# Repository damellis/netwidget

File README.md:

Examples of connected (internet of things) devices, built using the Arduino software, Eagle circuit design software, the ATmega1284P microcontroller, and the CC3000 wifi module.

The master branch contains just the files common to all the examples. See the following branches for the individual examples:

* display: has a screen to show the weather or other online data (https://github.com/damellis/netwidget/tree/display)
* pair: each device has touch sensing and an RGB LED to allow remote communication (https://github.com/damellis/netwidget/tree/pair)
* sensor: logging temperature sensor data to data.sparkfun.com (https://github.com/damellis/netwidget/tree/sensor)

For more information, see: http://diy-devices.com/workshops/connected-devices/

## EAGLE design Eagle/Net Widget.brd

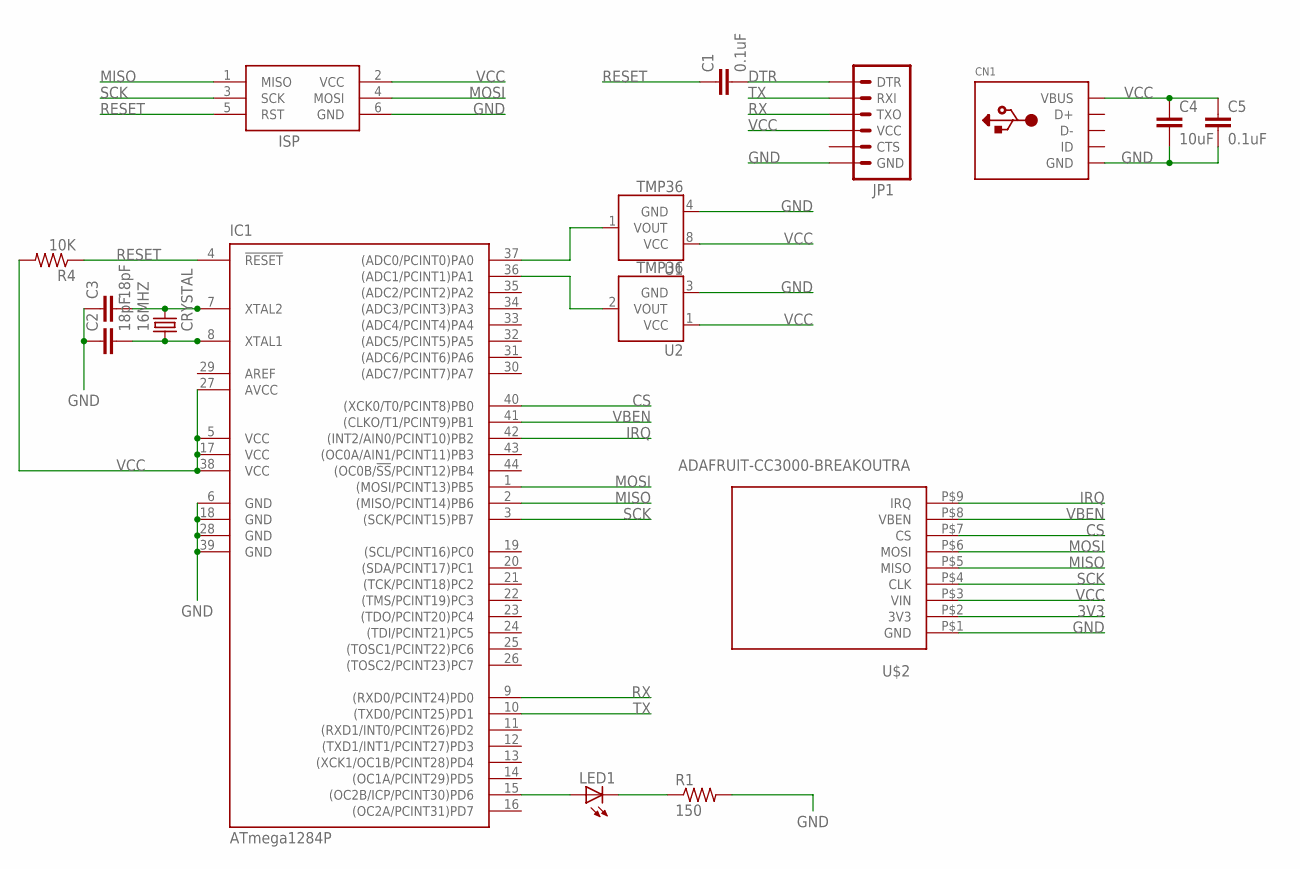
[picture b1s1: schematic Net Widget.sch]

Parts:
16MHZ: CRYSTAL; 2-SMD-5X3MM
C1, C5: 0.1uF; C1206
C2, C3: 18pF; C1206
C4: 10uF; C1206
CN1: USBPWR; USB-MINIB-POWER
IC1: ATmega1284P; TQFP44
ISP: AVRISP-6; AVRISP
JP1: ARDUINO_SERIAL_PROGRAMSMD; 1X06-SMD
LED1: LEDSMT1206; 1206
R1: 150; R1206
R4: 10K; R1206
U1: TMP36; SO08
U2: TMP36; TO-92
U$2: ADAFRUIT-CC3000-BREAKOUTRA; ADAFRUIT-CC3000-BREAKOUT-RA

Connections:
3V3: U$2.P$2 (3V3)
AREF: IC1.29 (AREF)
CS: IC1.40 ((XCK0/T0/PCINT8)PB0), U$2.P$7 (CS)
DTR: C1.2, JP1.1 (DTR)
GND: C2.1, C3.1, C4.2, C5.2, CN1.GND, IC1.6 (GND), IC1.18 (GND), IC1.28 (GND), IC1.39 (GND), ISP.6 (GND), JP1.6 (GND), R1.2, U1.4 (GND), U2.3 (GND), U$2.P$1 (GND)
IRQ: IC1.42 ((INT2/AIN0/PCINT10)PB2), U$2.P$9 (IRQ)
MISO: IC1.2 ((MISO/PCINT14)PB6), ISP.1 (MISO), U$2.P$5 (MISO)
MOSI: IC1.1 ((MOSI/PCINT13)PB5), ISP.4 (MOSI), U$2.P$6 (MOSI)
unnamed: IC1.37 ((ADC0/PCINT0)PA0), U1.1 (VOUT)
unnamed: IC1.36 ((ADC1/PCINT1)PA1), U2.2 (VOUT)
unnamed: IC1.15 ((OC2B/ICP/PCINT30)PD6), LED1.A
unnamed: LED1.C, R1.1
unnamed: 16MHZ.P$2 (2), C3.2, IC1.7 (XTAL2)
unnamed: 16MHZ.P$1 (1), C2.2, IC1.8 (XTAL1)
RESET: C1.1, IC1.4 (!RESET), ISP.5 (RST), R4.1
RX: IC1.9 ((RXD0/PCINT24)PD0), JP1.3 (TXO)
SCK: IC1.3 ((SCK/PCINT15)PB7), ISP.3 (SCK), U$2.P$4 (CLK)
TX: IC1.10 ((TXD0/PCINT25)PD1), JP1.2 (RXI)
VBEN: IC1.41 ((CLKO/T1/PCINT9)PB1), U$2.P$8 (VBEN)
VCC: C4.1, C5.1, CN1.VBUS, IC1.5 (VCC), IC1.17 (VCC), IC1.27 (AVCC), IC1.38 (VCC), ISP.2 (VCC), JP1.4 (VCC), R4.2, U1.8 (VCC), U2.1 (VCC), U$2.P$3 (VIN)

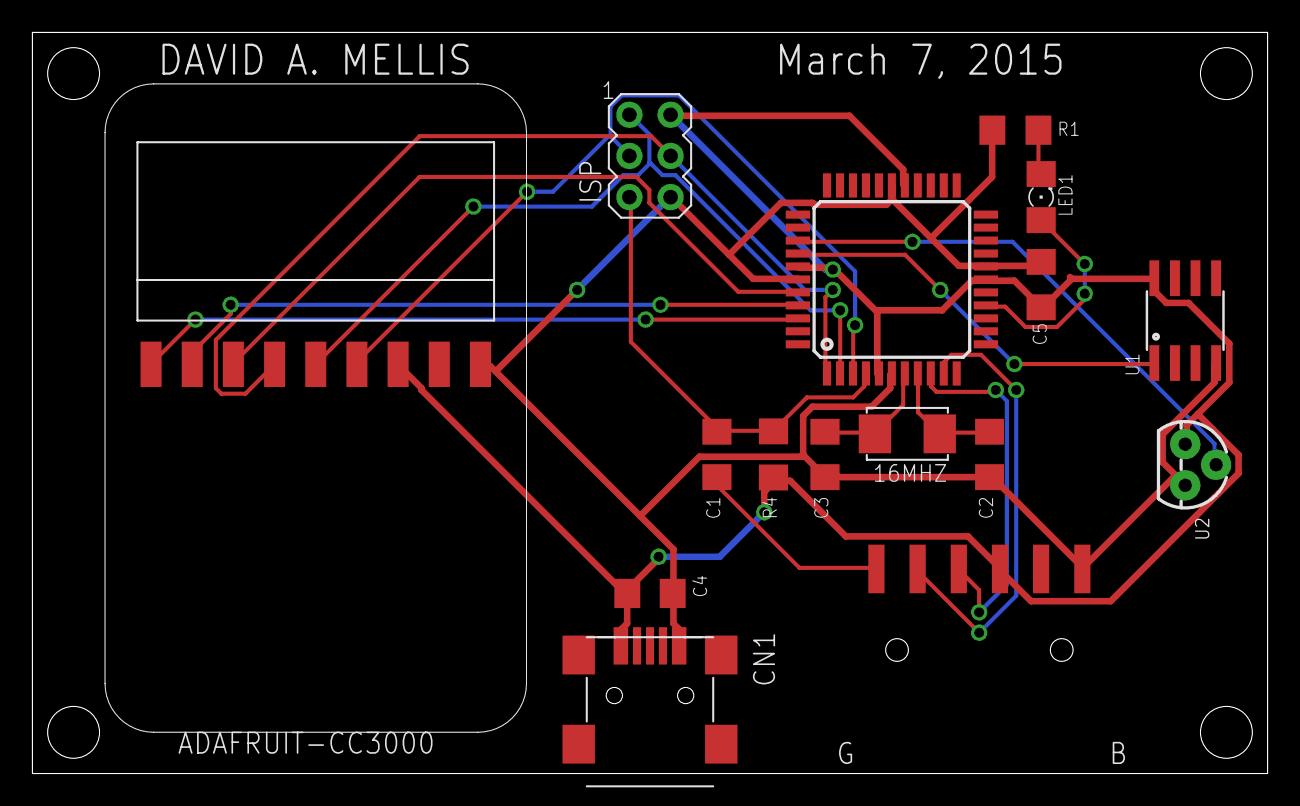
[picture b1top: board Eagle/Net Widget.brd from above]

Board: 2 copper layers, 76.2 x 45.7 mm, 16 parts (0 on the bottom side), 18 nets.

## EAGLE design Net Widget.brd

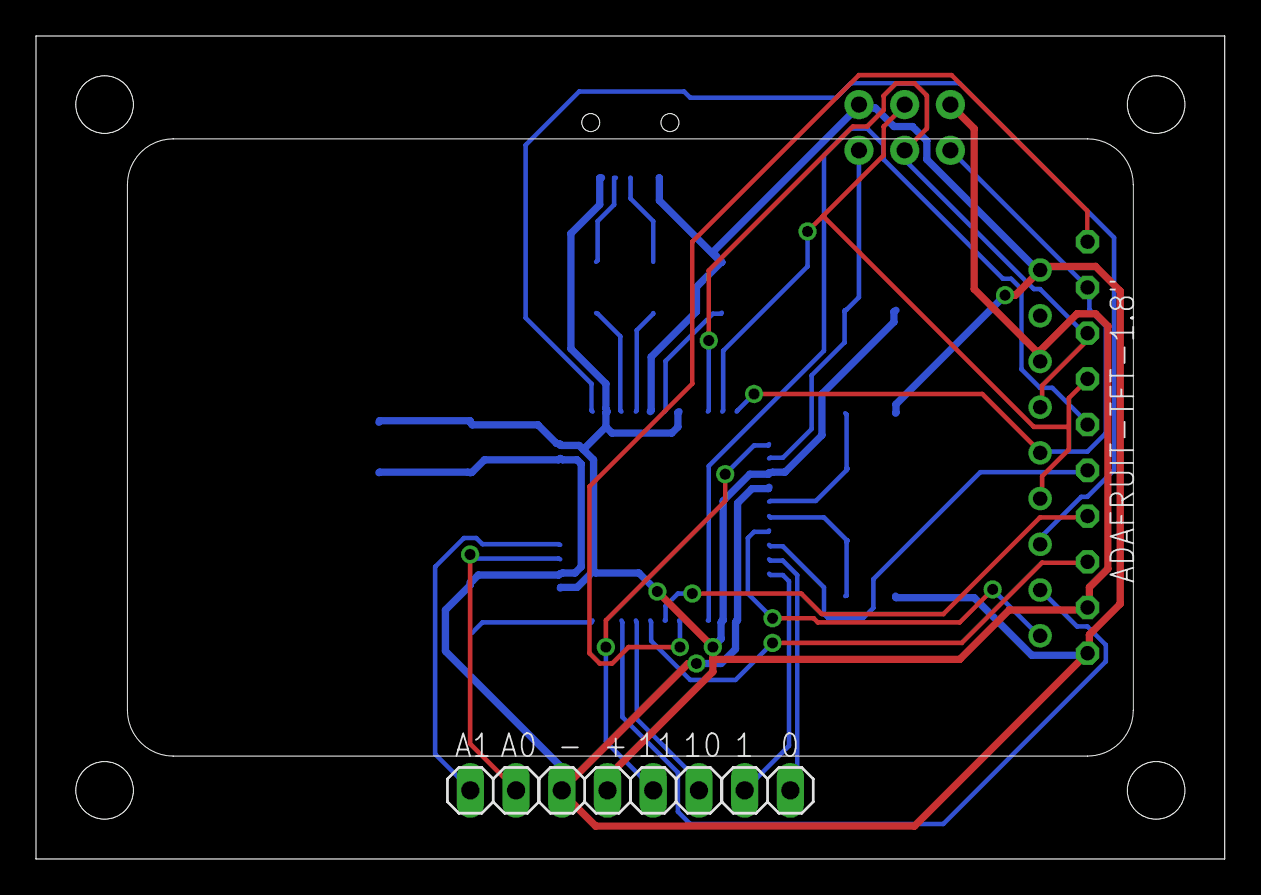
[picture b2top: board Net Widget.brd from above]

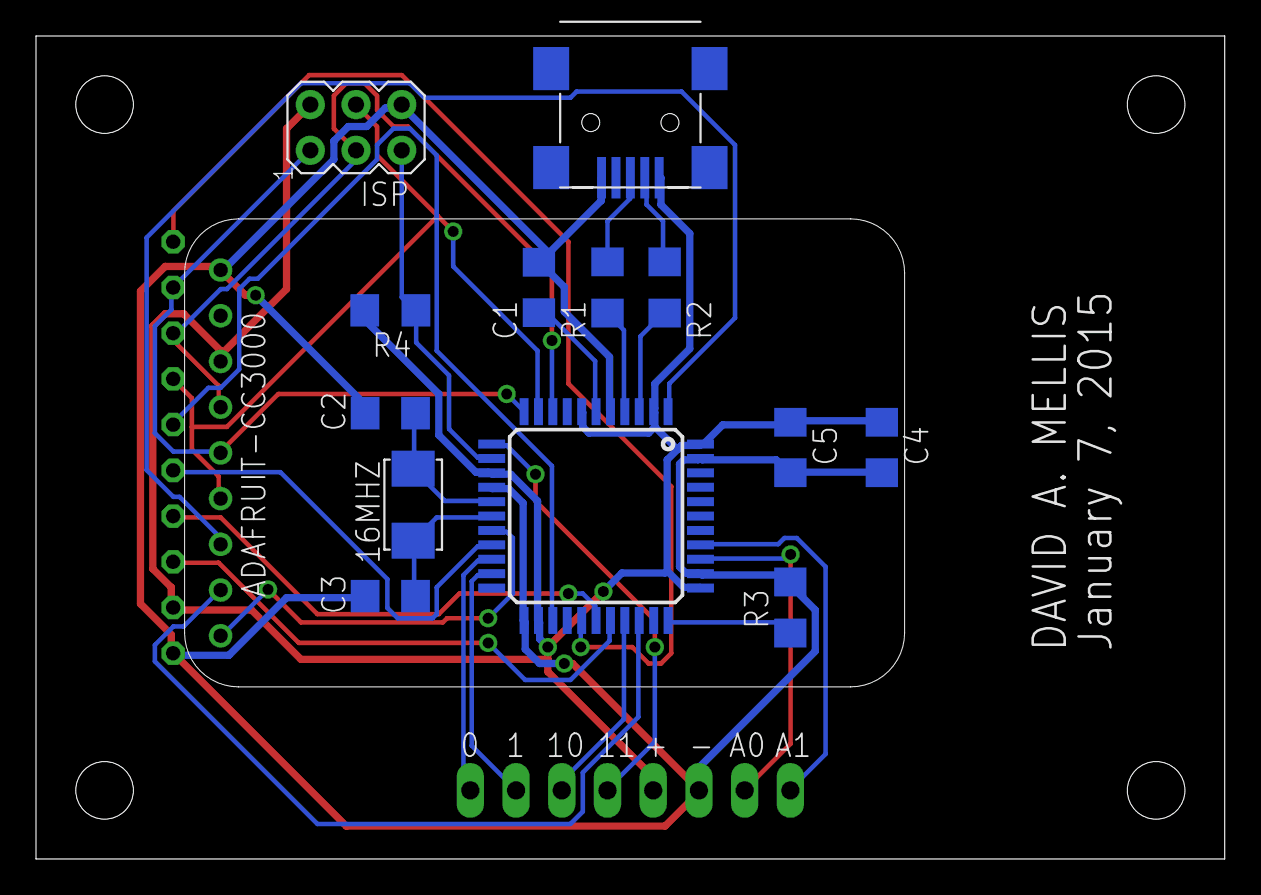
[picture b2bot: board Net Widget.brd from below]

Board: 2 copper layers, 66.0 x 45.7 mm, 19 parts (14 on the bottom side), 28 nets.

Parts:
16MHZ: CRYSTAL; 2-SMD-5X3MM
C1: 1uF; C1206
C2, C3: 18pF; C1206
C4: 10uF; C1206
C5: 0.1uF; C1206
CN1: USB-MINIB
ISP: AVRISP-6; AVRISP
JP1, JP2, JP3, JP4: 1X02
R1, R2: 22; R1206
R3, R4: 10K; R1206
U$1: ATMEGA32U4-AU; TQFP44
U$2: ADAFRUIT-CC3000-BREAKOUT
U$3: ADAFRUIT-TFT1.8-BREAKOUT

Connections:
A0: JP2.2, U$1.36
A1: JP2.1, U$1.37
CARD_CS: U$1.19, U$3.P$6
CS: U$1.1, U$2.P7
D0: JP1.2, U$1.20
D1: JP1.1, U$1.21
D10: JP3.2, U$1.30
D11: JP3.1, U$1.12
D+: R1.2, U$1.4
D-: R2.2, U$1.3
D/C: U$1.28, U$3.P$7
GND: C1.2, C2.1, C3.1, C4.2, C5.2, CN1.GND, ISP.6, JP4.2, R3.2, U$1.5, U$1.15, U$1.23, U$1.35, U$1.43, U$2.P1, U$3.P$10
IRQ: U$1.18, U$2.P9
LITE: U$1.27, U$3.P$1
MISO: ISP.1, U$1.11, U$2.P5, U$3.P$2
MOSI: ISP.4, U$1.10, U$2.P6, U$3.P$4
unnamed: CN1.D+, R1.1
unnamed: CN1.D-, R2.1
unnamed: C1.1, U$1.6
unnamed: R3.1, U$1.33
unnamed: 16MHZ.P$2, C3.2, U$1.17
unnamed: 16MHZ.P$1, C2.2, U$1.16
RESET: ISP.5, R4.1, U$1.13
SCK: ISP.3, U$1.9, U$2.P4, U$3.P$3
TFT_CS: U$1.25, U$3.P$5
TFT_RESET: U$1.29, U$3.P$8
VBEN: U$1.31, U$2.P8
VCC: C4.1, C5.1, CN1.VBUS, ISP.2, JP4.1, R4.2, U$1.2, U$1.7, U$1.14, U$1.24, U$1.34, U$1.44, U$2.P3, U$3.P$9

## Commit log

2015-01-12 Initial commit.
2015-01-19 Move Eagle files to sub-directory.
2015-01-19 Add Adafruit's CC3000, GFX, and ST7735 libraries for Arduino.
2015-01-19 Add example of using Temboo+CC3000 to get Yahoo Weather information.
2015-01-19 Switch to Net Widget.lbr and increase hole sizes.
2015-01-19 Replace ATmega32U4 w/ ATmega1284P.
    Initial pass. Adds an FTDI header and replaces the Mini-USB footprint.
2015-01-20 Clean up library and board.
    Add breakout headers, move components into Net Widget library, switch
    to Mini USB B connector with holes for mounting posts, silk screen
    layout, etc.
2015-01-20 Arduino test sketch for TFT display.
2015-01-20 Include TFT display in code.
2015-01-20 Generate gerbers.
2015-01-23 Add board definition. Update example pin numbers.
2015-01-26 Adjust pin numbers for ATmega1284 board.
2015-01-26 Show weather on the TFT display.
2015-01-28 Add TMP36 and packages for CC3000 / FTDI.
2015-01-28 Replace TFT w/ temperature sensor.
2015-01-28 Ignore Eagle backup files.
2015-01-28 Match CS and VBEN to Wicked Devices wildfire.
2015-01-28 Ignore Eagle auto-router job files.
2015-01-28 Auto-route board.
2015-01-29 Re-route w/ more space between pads and vias.
2015-01-29 Add WickedDevice Wildfire Arduino hardware files.
2015-01-29 Remove temp sensor; add LEDs and touch.
2015-01-29 Add CapacitiveSensor library.
2015-01-29 Re-arrange LEDs and touch point.
2015-01-29 Ditto.
2015-01-29 More tweaks.
2015-01-29 Tweak.
2015-01-29 Route.
2015-01-30 Add alligator clip connector and adjust silkscreen
2015-01-30 Silk screen adjustments.
2015-02-04 Arduino capacitive -> RGB LED sketch.
2015-02-04 Add WickedDevice hardware files.
2015-02-04 Use built-in platform.txt for WickedDevice boards
2015-02-04 Fix bootloader path for WildFire.
2015-02-04 Update tools for WildFire v2.
2015-02-04 Update pin numbers to match board.
2015-02-05 Add layers for acrylic enclosure.
2015-02-05 Update CC3000 pin numbers.
2015-02-05 RGB LED test Arduino sketch.
2015-02-05 Add layers for acrylic base and top.
2015-02-05 Add Phant library and Arduino sketch.
2015-02-06 Remove use of Phant library.
2015-02-12 Acrylic enclosure.
2015-02-12 SMD pads for breakout boards and layout.
    Moved a bunch of things around after switching to right-angle
    surface-mount headers for the CC3000 and TFT breakout boards.
2015-02-12 Ignore more auto-generated Eagle files.
2015-02-12 Remove broken-out pins.
2015-02-19 Update CC3000 library from Adafruit.
2015-02-19 Add SPI transactions to ST7735 TFT library.
    Otherwise, the CC3000 seems to interfere with communication to the
    display.
2015-02-19 Add additional debugging messages.
2015-02-19 Sketch to test bmp display.
2015-02-19 Ignore TembooAccount.h credential file.
2015-02-20 Move CC3000, re-route, silk screen cleanup.
2015-02-20 Sketch to show a dummy weather bitmap.
2015-03-06 Add WickedDevice hardware definitions.
2015-03-06 Tempo weather Arduino sketch for this PCB.
2015-03-06 Update pins for WildFire board definition.
2015-03-06 Update pins for WildFire mapping and this PCB.
2015-03-07 Ignore .pro files.
2015-03-07 Match pin numbers to WildFire; route.
2015-03-07 Update pins for WildFire / new PCB.
2015-03-07 Surface-mount FTDI header. Add LED.
2015-03-14 Remove Sanguino hardware definitions.
2015-03-14 Update pins for new PCB.
2015-03-14 Remove Sanguine board definition files.
2015-03-14 Update to current PCB.
2015-03-14 Paired Arduino devices communicating using Phant.
    Posting to one channel and reading from the other. Uses touch
    (capacitive sensing) input and RGB LED output.
2015-03-14 Remove Gerber files from other board.
2015-03-21 Remove Weather Arduino example from other branch.
2015-03-21 Try to make slightly more robust.
2015-03-21 Ignore touches with repeated timestamps.
2015-03-22 Add #defines
2015-03-23 Clean up Eagle library.
2015-03-23 Create README.md.
2015-04-26 Improve weather display.
2015-05-27 3D-printed enclosure.
2016-05-18 Small updates to code.

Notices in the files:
parts and their libraries:
SparkFun-Connectors: Licensing: Creative Commons ShareAlike 4.0 International - https://creativecommons.org/licenses/by-sa/4.0
